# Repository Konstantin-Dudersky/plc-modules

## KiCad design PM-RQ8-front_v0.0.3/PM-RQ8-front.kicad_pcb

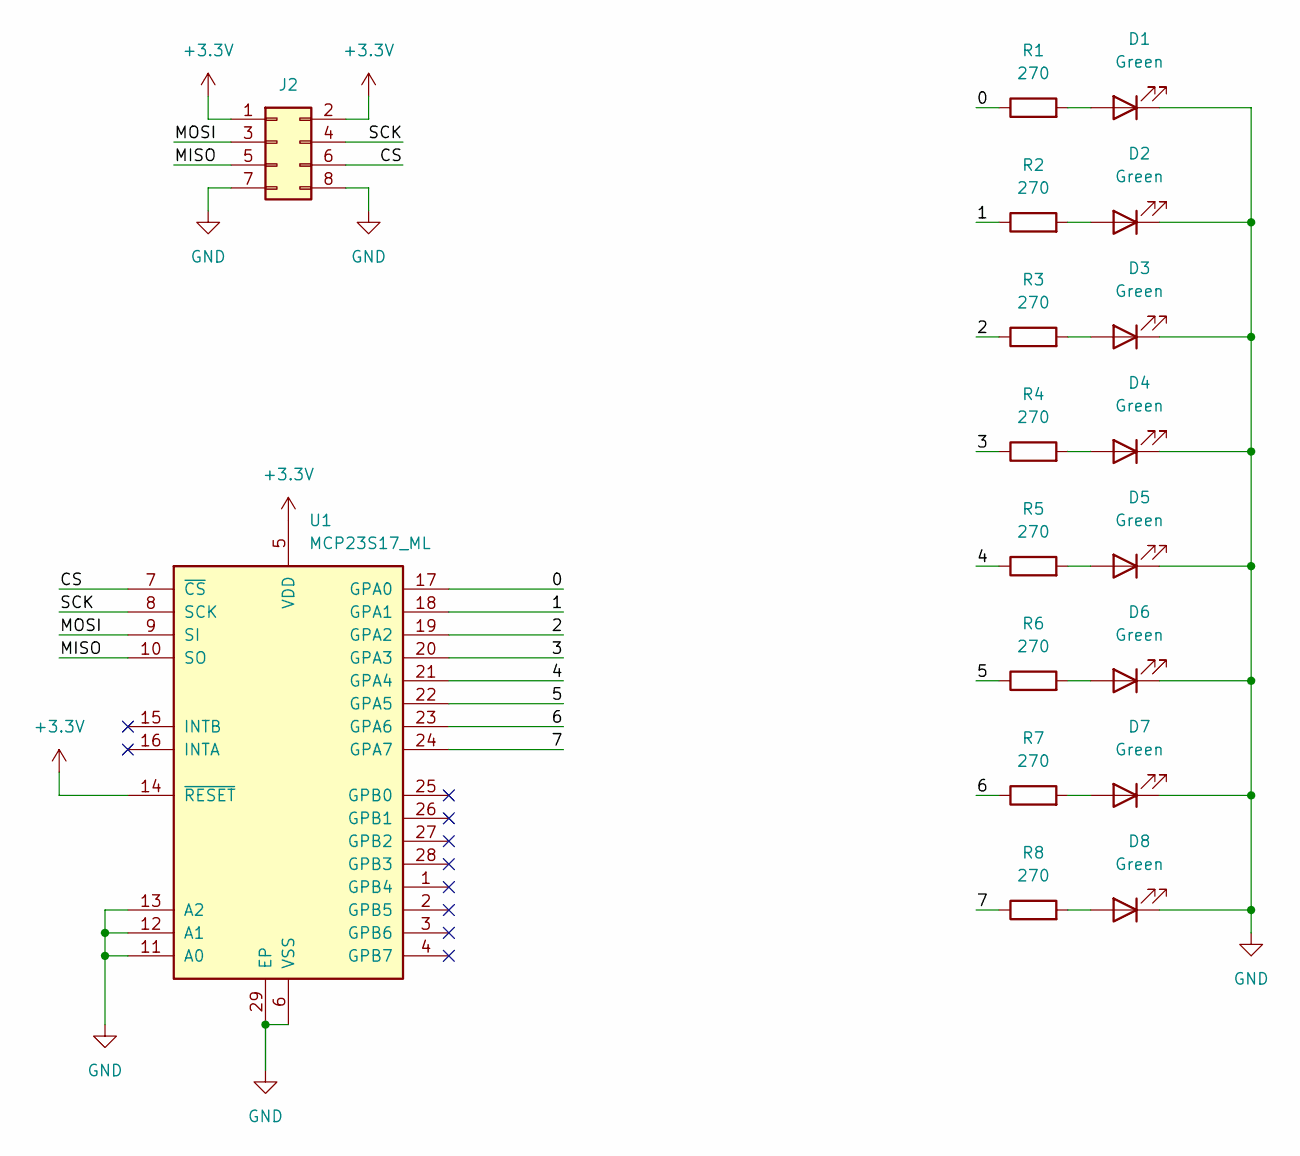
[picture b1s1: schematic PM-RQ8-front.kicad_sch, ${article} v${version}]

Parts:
D1, D2, D3, D4, D5, D6, D7, D8: Green; LED_1206_3216Metric_ReverseMount_Hole1.8x2.4mm; part_ipn LED_green_1206_reverse
J2: PinHeader_02x04_P2.54_THT_angle; PinHeader_2x04_P2.54mm_Horizontal; part_ipn PinHeader_02x04_P2.54_THT_angle
R1, R2, R3, R4, R5, R6, R7, R8: 270; R_1206_3216Metric_Pad1.30x1.75mm_HandSolder; part_ipn R_270_1206_1%
U1: MCP23S17_ML; QFN-28-1EP_6x6mm_P0.65mm_EP4.25x4.25mm; part_ipn MCP23S17-E/ML

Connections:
+3.3V: J2.1, J2.2, U1.5 (VDD), U1.14 (~RESET)
/0: R1.1, U1.17 (GPA0)
/1: R2.1, U1.18 (GPA1)
/2: R3.1, U1.19 (GPA2)
/3: R4.1, U1.20 (GPA3)
/4: R5.1, U1.21 (GPA4)
/5: R6.1, U1.22 (GPA5)
/6: R7.1, U1.23 (GPA6)
/7: R8.1, U1.24 (GPA7)
/CS: J2.6, U1.7 (~CS)
/MISO: J2.5, U1.10 (SO)
/MOSI: J2.3, U1.9 (SI)
/SCK: J2.4, U1.8 (SCK)
GND: D1.1 (K), D2.1 (K), D3.1 (K), D4.1 (K), D5.1 (K), D6.1 (K), D7.1 (K), D8.1 (K), J2.7, J2.8, U1.6 (VSS), U1.11 (A0), U1.12 (A1), U1.13 (A2), U1.29 (EP)
unnamed: D1.2 (A), R1.2
unnamed: D2.2 (A), R2.2
unnamed: D3.2 (A), R3.2
unnamed: D4.2 (A), R4.2
unnamed: D5.2 (A), R5.2
unnamed: D6.2 (A), R6.2
unnamed: D7.2 (A), R7.2
unnamed: D8.2 (A), R8.2

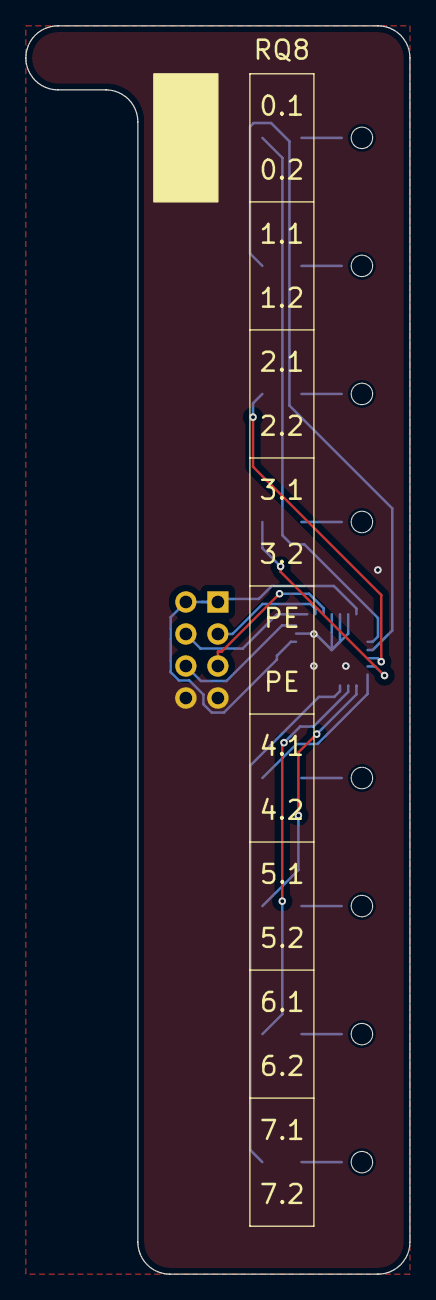
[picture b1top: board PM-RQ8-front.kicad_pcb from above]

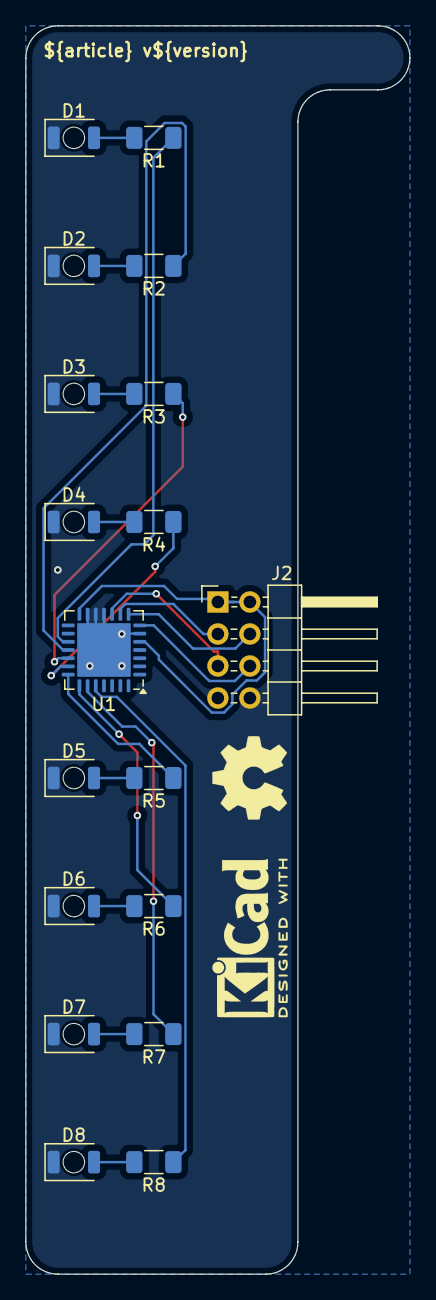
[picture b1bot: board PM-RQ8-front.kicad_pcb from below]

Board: 2 copper layers, 30.5 x 99.1 mm, 19 parts (19 on the bottom side), 22 nets.

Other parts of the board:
Logo_kicad: KiCad-Logo2_5mm_SilkScreen

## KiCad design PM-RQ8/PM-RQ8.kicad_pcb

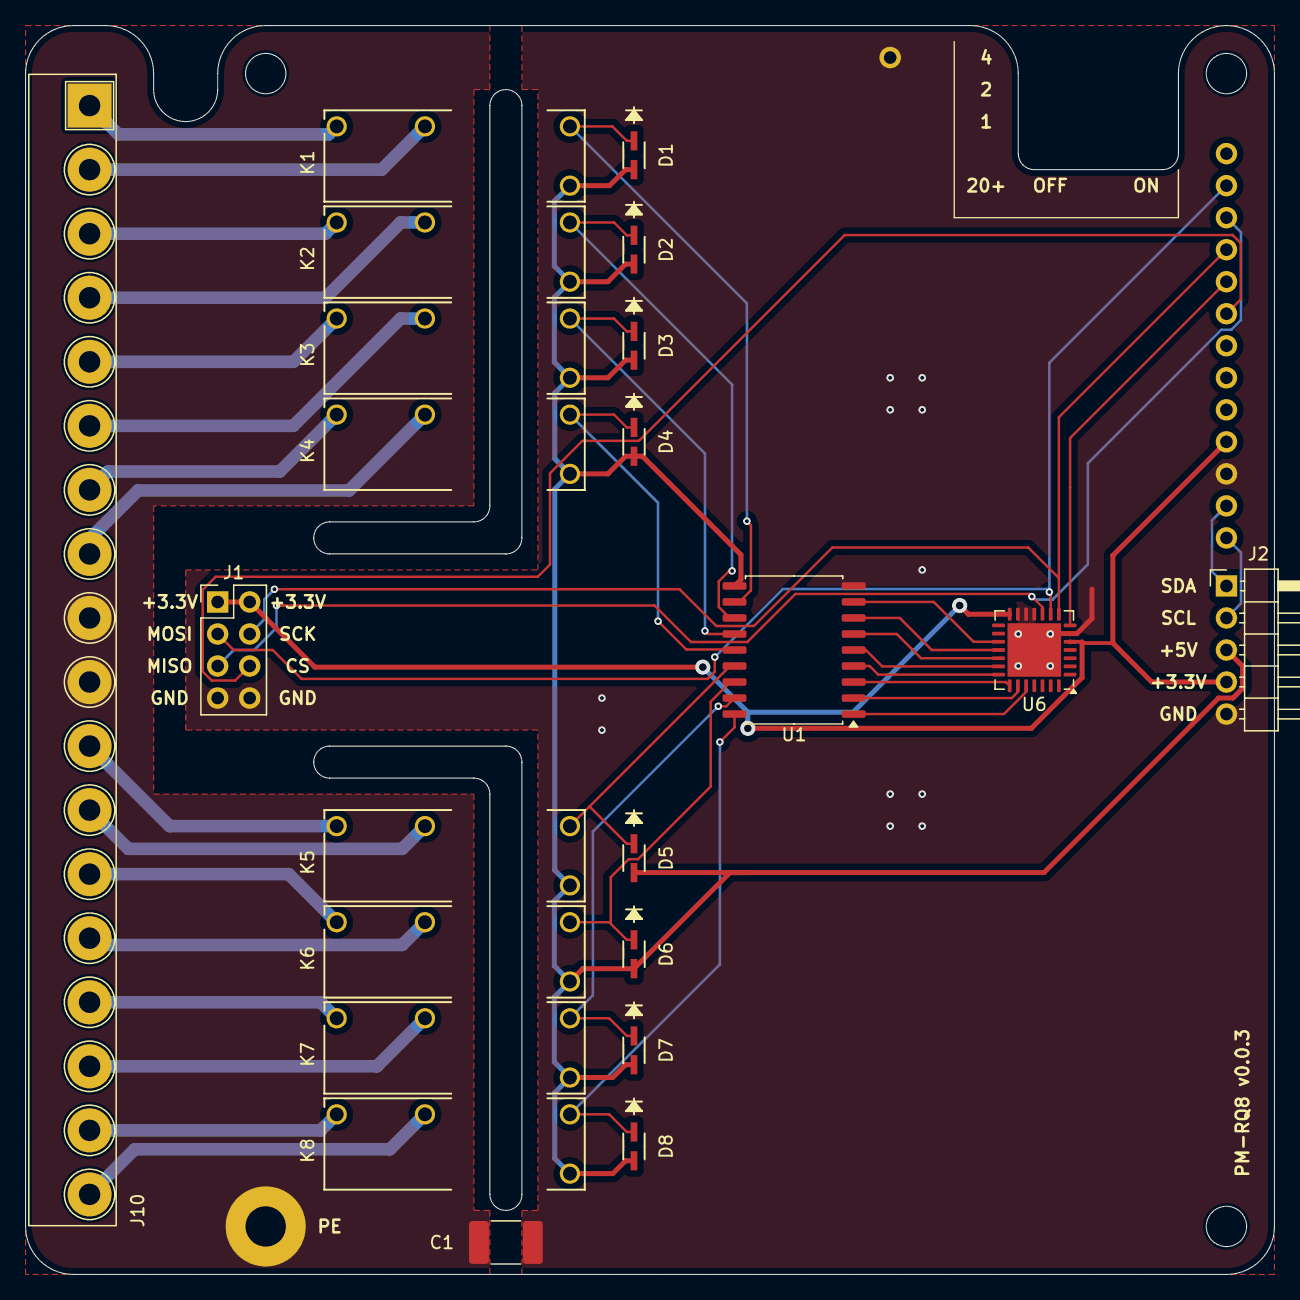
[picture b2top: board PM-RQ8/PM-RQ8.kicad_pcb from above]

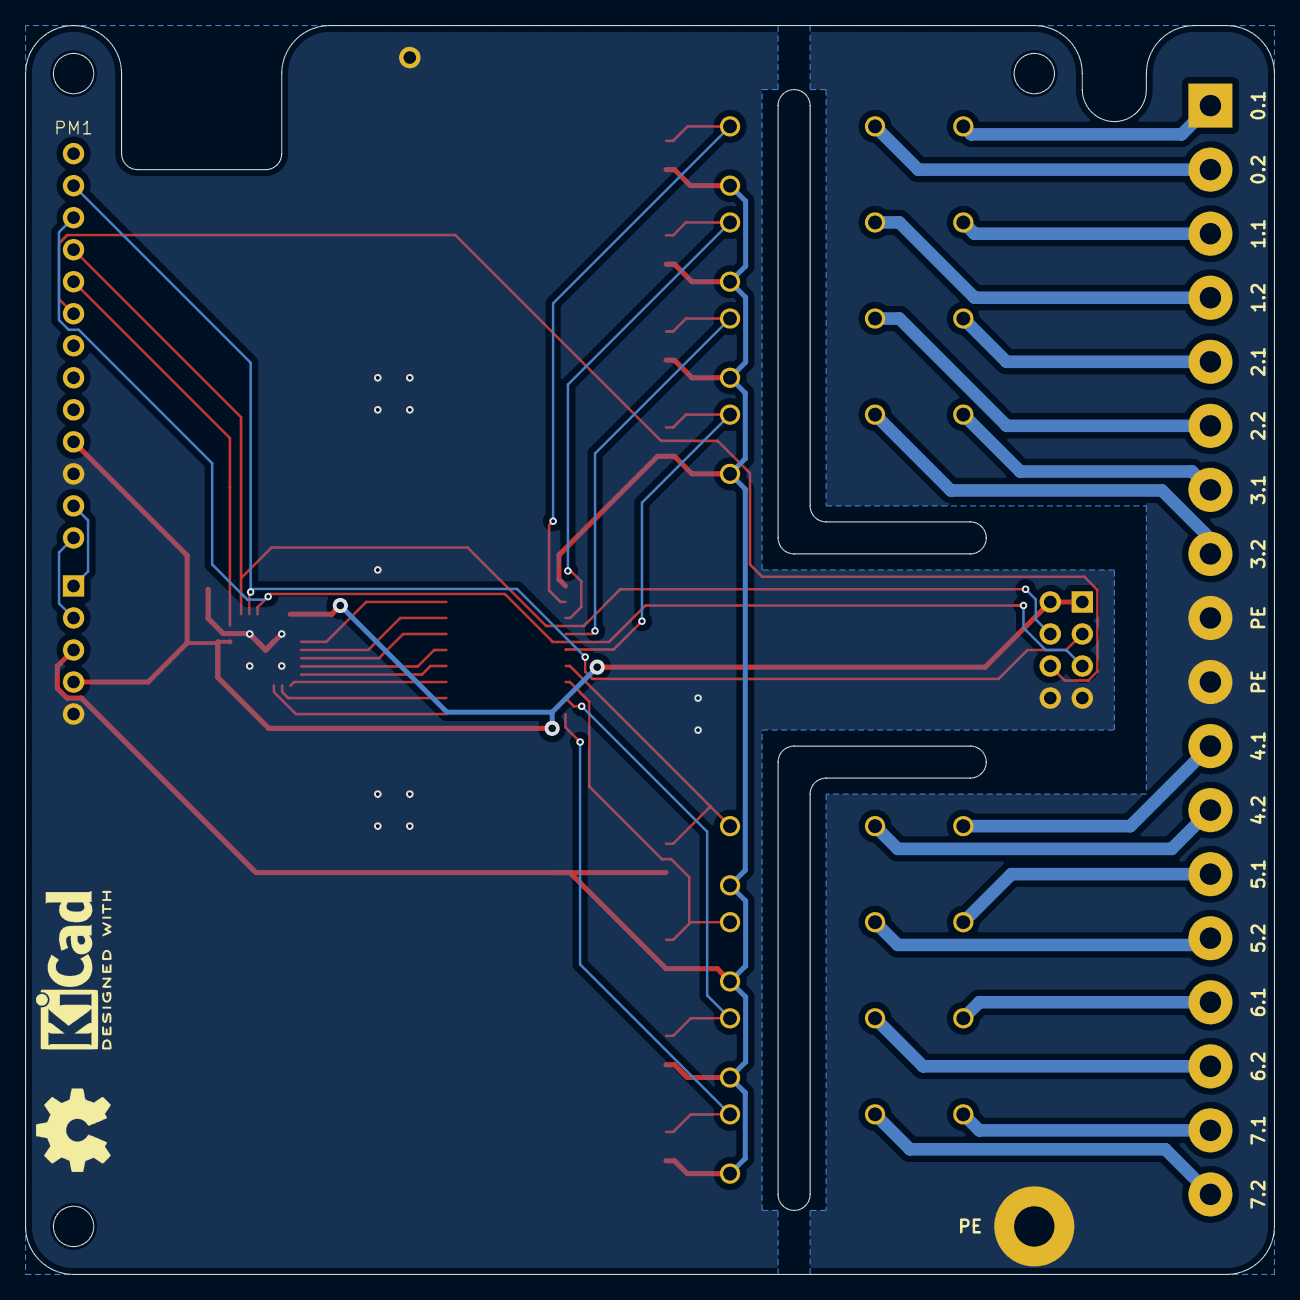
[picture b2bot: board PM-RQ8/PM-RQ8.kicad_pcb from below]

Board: 2 copper layers, 99.1 x 99.1 mm, 29 parts (3 on the bottom side), 43 nets.

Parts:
C1: 4.7nF 2kV; C_1812_4532Metric_Pad1.57x3.40mm_HandSolder
D1, D2, D3, D4, D5, D6, D7, D8: BAT20J; SOD-323_STM-M
H1, H2, H3: MountingHole; MountingHole_3.2mm_M3
J1: PM-front-02x04
J2: PinHeader_01x05_P2.54_THT_angle; PinHeader_1x05_P2.54mm_Horizontal
J10: 2EDGR-5.08-18P; Degson_2EDGR-5.08-18P
K1, K2, K3, K4, K5, K6, K7, K8: G5NB-1A-E-DC5; G5NB-1A-E_DC12_RELAY_G5NB-1A_DC5_OMR
PE1: PE
PM1: PM-ESP32C3
U1: ULN2803A
U6: MCP23S17_ML; QFN-28-1EP_6x6mm_P0.65mm_EP4.25x4.25mm
kicad_logo: KiCad-Logo2_5mm_SilkScreen
oshw_logo: OSHW-Symbol_6.7x6mm_SilkScreen

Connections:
+3.3V: J1.1, J1.2, J2.4, PM1.10 (+3.3V), U6.5 (VDD), U6.14 (~RESET)
+5V: D1.2, D2.2, D3.2, D4.2, D5.2, D6.2, D7.2, D8.2, J2.3, K1.4, K2.4, K3.4, K4.4, K5.4, K6.4, K7.4, K8.4, U1.10 (COM)
/CS1: PM1.5 (GPIO8), U6.7 (~CS)
/CS2: J1.6, PM1.6 (GPIO7)
/K1: D1.1, K1.1, U1.11 (O8)
/K1_exp: U1.8 (I8), U6.17 (GPA0)
/K2: D2.1, K2.1, U1.12 (O7)
/K2_exp: U1.7 (I7), U6.18 (GPA1)
/K3: D3.1, K3.1, U1.13 (O6)
/K3_exp: U1.6 (I6), U6.19 (GPA2)
/K4: D4.1, K4.1, U1.14 (O5)
/K4_exp: U1.5 (I5), U6.20 (GPA3)
/K5: D5.1, K5.1, U1.15 (O4)
/K5_exp: U1.4 (I4), U6.21 (GPA4)
/K6: D6.1, K6.1, U1.16 (O3)
/K6_exp: U1.3 (I3), U6.22 (GPA5)
/K7: D7.1, K7.1, U1.17 (O2)
/K7_exp: U1.2 (I2), U6.23 (GPA6)
/K8: D8.1, K8.1, U1.18 (O1)
/K8_exp: U1.1 (I1), U6.24 (GPA7)
/MISO: J1.5, PM1.3 (GPIO3), U6.10 (SO)
/MOSI: J1.3, PM1.2 (GPIO2), U6.9 (SI)
/SCK: J1.4, PM1.4 (GPIO9), U6.8 (SCK)
/SCL: J2.2, PM1.13 (SCL)
/SDA: J2.1, PM1.12 (SDA)
GND: C1.2, J1.7, J1.8, J2.5, PM1.11 (GND), PM1.14 (GND), U1.9 (GND), U6.6 (VSS), U6.11 (A0), U6.12 (A1), U6.13 (A2), U6.29 (EP)
unnamed: J10.1, K1.3
unnamed: J10.2, K1.2
unnamed: J10.3, K2.3
unnamed: J10.4, K2.2
unnamed: J10.5, K3.3
unnamed: J10.6, K3.2
unnamed: J10.7, K4.3
unnamed: J10.8, K4.2
unnamed: J10.11, K5.3
unnamed: J10.12, K5.2
unnamed: J10.13, K6.3
unnamed: J10.14, K6.2
unnamed: J10.15, K7.3
unnamed: J10.16, K7.2
unnamed: J10.17, K8.3
unnamed: J10.18, K8.2
PE: C1.1, J10.9, J10.10, PE1.1

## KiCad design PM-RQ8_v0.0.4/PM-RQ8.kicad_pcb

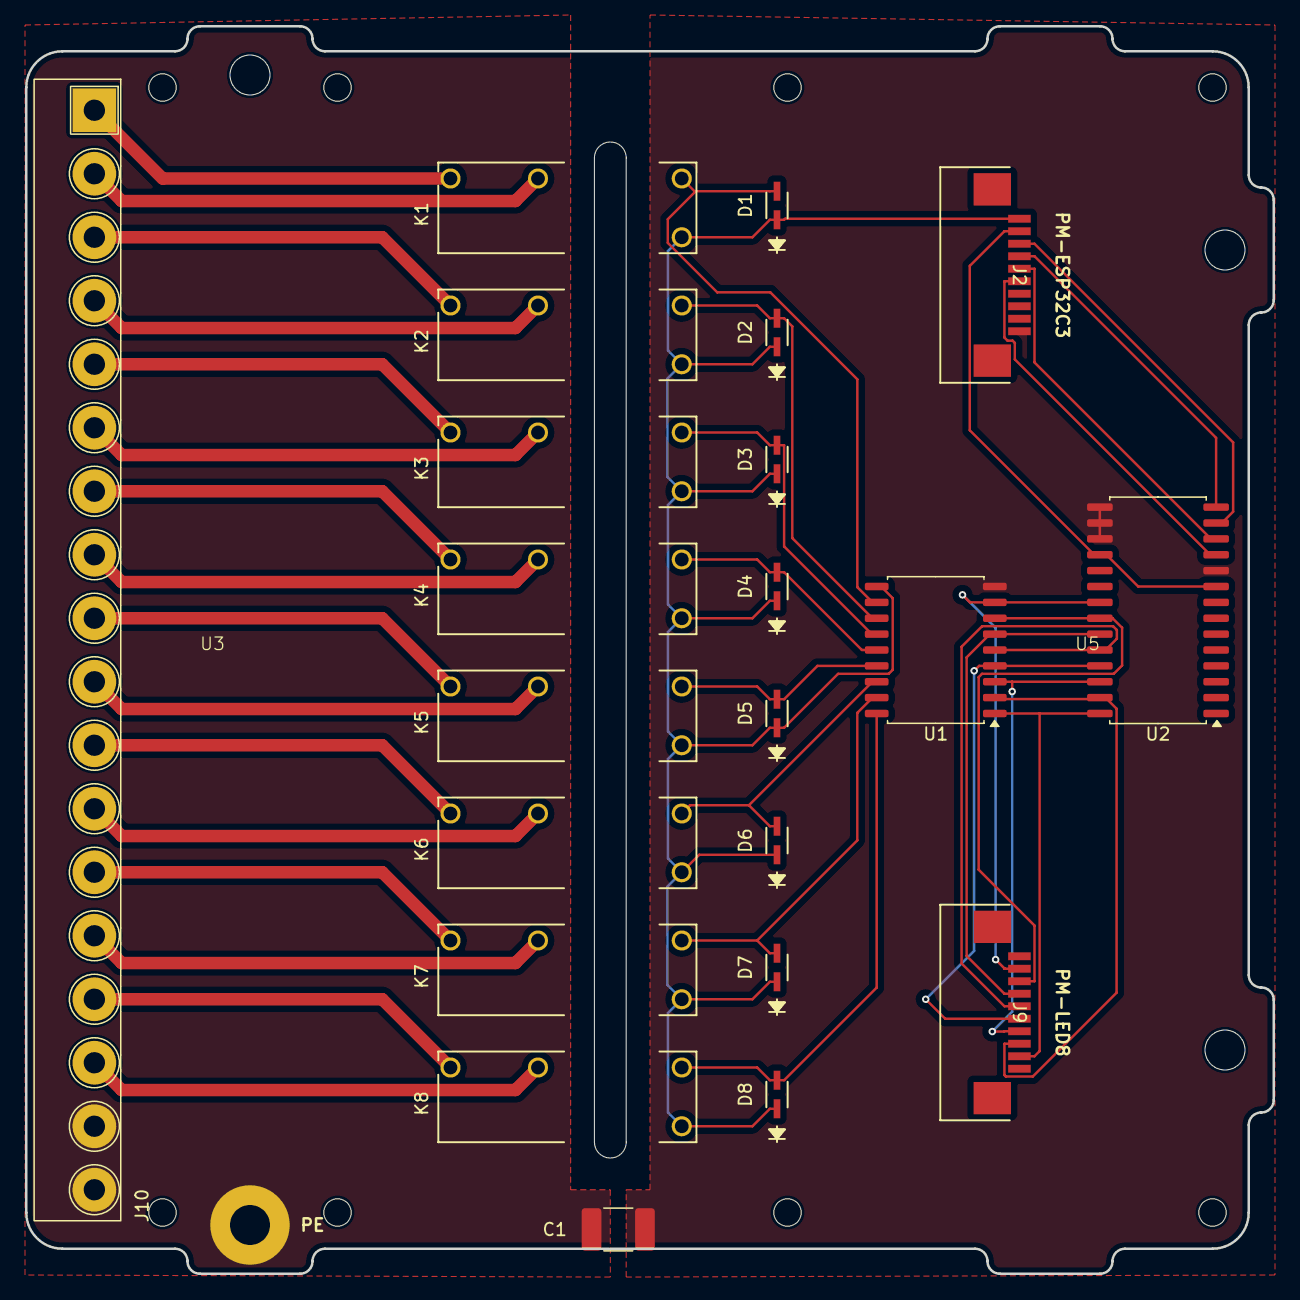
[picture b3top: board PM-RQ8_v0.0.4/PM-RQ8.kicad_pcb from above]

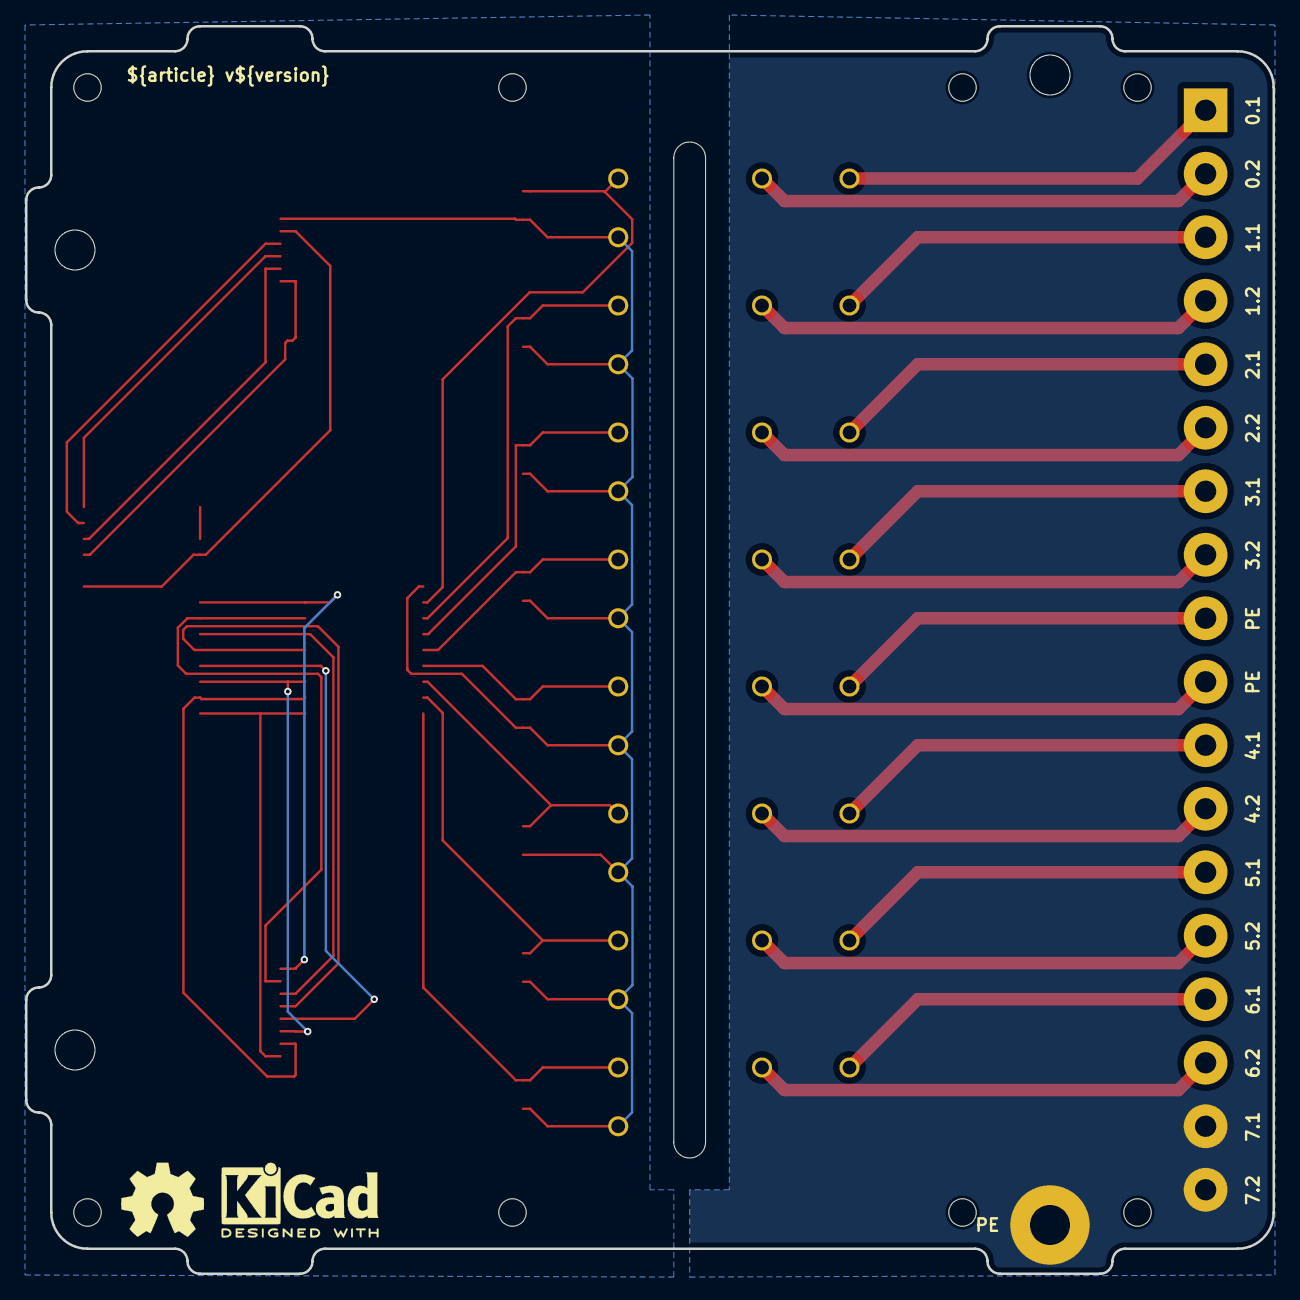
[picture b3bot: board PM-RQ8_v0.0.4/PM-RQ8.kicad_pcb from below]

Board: 2 copper layers, 99.8 x 99.8 mm, 30 parts (2 on the bottom side), 40 nets.

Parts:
C1: 4.7nF 2kV; C_1812_4532Metric_Pad1.57x3.40mm_HandSolder
D1, D2, D3, D4, D5, D6, D7, D8: BAT20J; SOD-323_STM-M
H1, H2, H3: MountingHole; MountingHole_3.2mm_M3
J2, J9: AFA07-S10FCC-00; CONN10_AFA07-S10_JUS
J10: 2EDGR-5.08-18P; Degson_2EDGR-5.08-18P
K1, K2, K3, K4, K5, K6, K7, K8: G5NB-1A-E-DC5; G5NB-1A-E_DC12_RELAY_G5NB-1A_DC5_OMR
PE1: PE
U1: ULN2803A
U2: MCP23S17_SO; SOIC-28W_7.5x17.9mm_P1.27mm
U3: PM-LED8_v0.0.1; PM-LED_v0.0.1
U5: PM-ESP32C3_v0.0.2
kicad_logo: KiCad-Logo2_5mm_SilkScreen
oshw_logo: OSHW-Symbol_6.7x6mm_SilkScreen

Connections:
+3.3V: J2.2, U2.9 (VDD), U2.18 (~RESET)
+5V: D1.1, D2.1, D3.1, D4.1, D5.1, D6.1, D7.1, D8.1, J2.1, K1.4, K2.4, K3.4, K4.4, K5.4, K6.4, K7.4, K8.4, U1.10 (COM)
/CS: J2.6, U2.11 (~CS)
/K1: D1.2, K1.1, U1.11 (O8)
/K1_exp: J9.2, U1.8 (I8), U2.21 (GPA0)
/K2: D2.2, K2.1, U1.12 (O7)
/K2_exp: J9.3, U1.7 (I7), U2.22 (GPA1)
/K3: D3.2, K3.1, U1.13 (O6)
/K3_exp: J9.4, U1.6 (I6), U2.23 (GPA2)
/K4: D4.2, K4.1, U1.14 (O5)
/K4_exp: J9.5, U1.5 (I5), U2.24 (GPA3)
/K5: D5.2, K5.1, U1.15 (O4)
/K5_exp: J9.6, U1.4 (I4), U2.25 (GPA4)
/K6: D6.2, K6.1, U1.16 (O3)
/K6_exp: J9.7, U1.3 (I3), U2.26 (GPA5)
/K7: D7.2, K7.1, U1.17 (O2)
/K7_exp: J9.8, U1.2 (I2), U2.27 (GPA6)
/K8: D8.2, K8.1, U1.18 (O1)
/K8_exp: J9.9, U1.1 (I1), U2.28 (GPA7)
/MISO: J2.4, U2.14 (SO)
/MOSI: J2.3, U2.13 (SI)
/SCK: J2.5, U2.12 (SCK)
GND: C1.2, J2.10, J9.10, U1.9 (GND), U2.10 (VSS), U2.15 (A0), U2.16 (A1), U2.17 (A2)
unnamed: J10.1, K1.3
unnamed: J10.2, K1.2
unnamed: J10.3, K2.3
unnamed: J10.4, K2.2
unnamed: J10.5, K3.3
unnamed: J10.6, K3.2
unnamed: J10.7, K4.3
unnamed: J10.8, K4.2
unnamed: J10.9, K5.3
unnamed: J10.10, K5.2
unnamed: J10.11, K6.3
unnamed: J10.12, K6.2
unnamed: J10.13, K7.3
unnamed: J10.14, K7.2
unnamed: J10.15, K8.3
unnamed: J10.16, K8.2
PE: C1.1, J10.17, J10.18, PE1.1

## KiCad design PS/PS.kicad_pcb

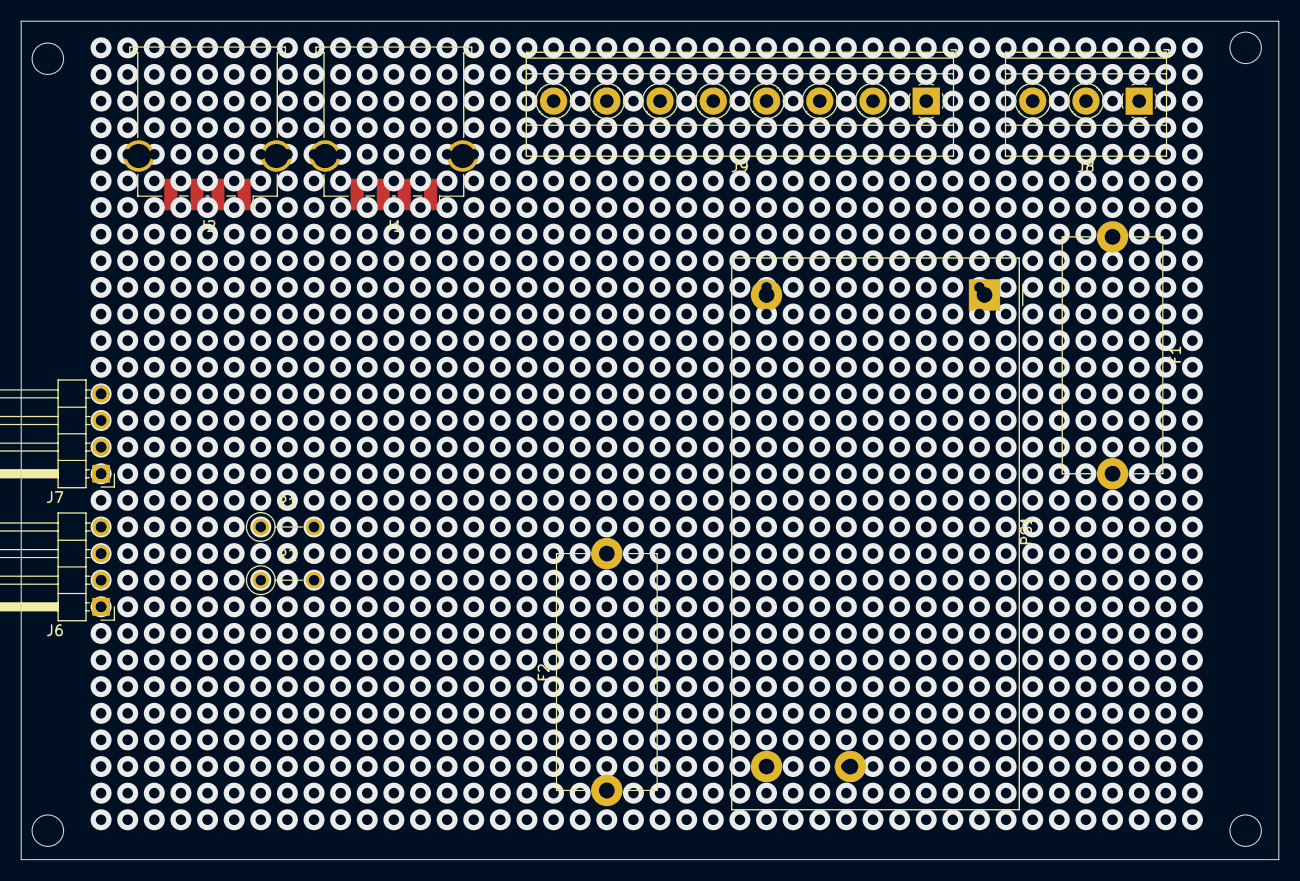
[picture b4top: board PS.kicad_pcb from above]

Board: 2 copper layers, 120.0 x 80.0 mm, 11 parts (0 on the bottom side), 9 nets, no tracks yet.

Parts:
F1, F2: Fuse; Fuseholder_Cylinder-5x20mm_Stelvio-Kontek_PTF78_Horizontal_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
J1, J2: USB_A; USB_A_TE_292303-7_Horizontal
J6, J7: PinHeader_01x04_angle; PinHeader_1x04_P2.54mm_Horizontal
J8: Conn_01x03_Socket; TerminalBlock_Phoenix_MKDS-1,5-3-5.08_1x03_P5.08mm_Horizont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
J9: Terminal_01x08_Socket; TerminalBlock_Phoenix_MKDS-1,5-8-5.08_1x08_P5.08mm_Horizont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
PS1: IRM-20-5; Converter_ACDC_MeanWell_IRM-20-xx_THT
R1, R2: 3.3к; R_Axial_DIN0207_L6.3mm_D2.5mm_P5.08mm_Vertical

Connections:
/3.3V: J7.2, R1.2, R2.2
/5V: F2.2, J1.1 (VBUS), J2.1 (VBUS), J6.2, J9.1, J9.3
/GND: J1.4 (GND), J2.4 (GND), J6.3, J9.2, J9.4, PS1.3 (-Vo)
/SCL: J6.1, J7.1, R2.1
/SDA: J6.4, J7.3, R1.1
unnamed: F1.1, J8.1
unnamed: J8.2, PS1.2 (AC/N)
unnamed: F2.1, PS1.4 (+Vo)
unnamed: F1.2, PS1.1 (AC/L)

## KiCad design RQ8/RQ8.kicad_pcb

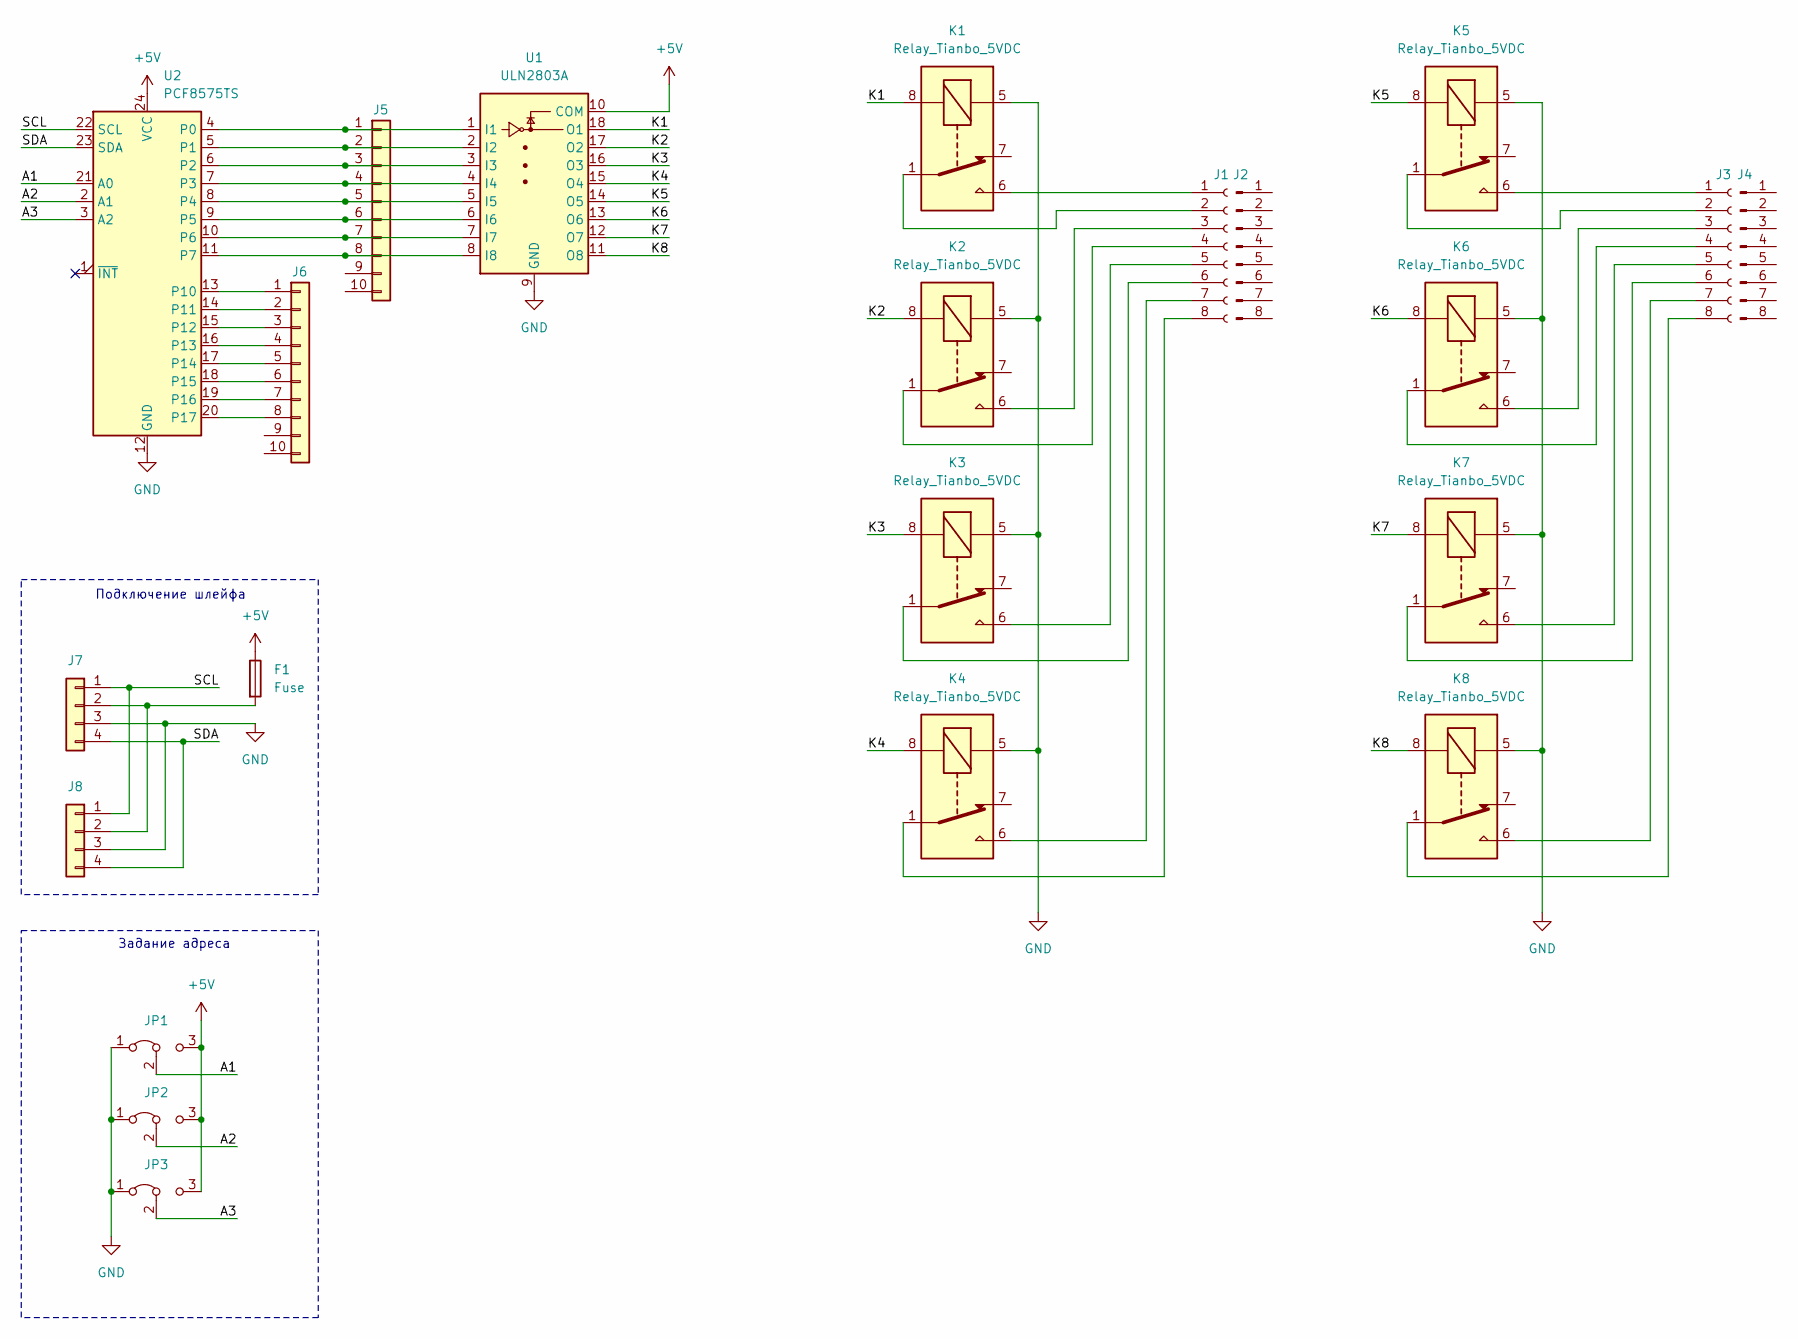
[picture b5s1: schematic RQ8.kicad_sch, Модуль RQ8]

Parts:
F1: Fuse; Fuseholder_Cylinder-5x20mm_Stelvio-Kontek_PTF78_Horizontal_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
J1, J3: Terminal_01x08_Socket; TerminalBlock_Phoenix_MKDS-1,5-8-5.08_1x08_P5.08mm_Horizont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
J2, J4: Conn_01x08_Pin
J5, J6: Conn_01x10; PinHeader_1x10_P2.54mm_Vertical
J7, J8: PinHeader_01x04_angle; PinHeader_1x04_P2.54mm_Horizontal
JP1, JP2, JP3: Jumper_3_Bridged12; PinHeader_1x03_P2.54mm_Vertical
K1, K2, K3, K4, K5, K6, K7, K8: Relay_Tianbo_5VDC; Relay_SPDT_HJR-4102
U1: ULN2803A; DIP-18_W7.62mm
U2: PCF8575TS; SSOP-24_5.3x8.2mm_P0.65mm

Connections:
+5V: F1.1, JP1.3 (B), JP2.3 (B), JP3.3 (B), U1.10 (COM), U2.24 (VCC)
/A1: JP1.2 (C), U2.21 (A0)
/A2: JP2.2 (C), U2.2 (A1)
/A3: JP3.2 (C), U2.3 (A2)
/K1: K1.8, U1.18 (O1)
/K2: K2.8, U1.17 (O2)
/K3: K3.8, U1.16 (O3)
/K4: K4.8, U1.15 (O4)
/K5: K5.8, U1.14 (O5)
/K6: K6.8, U1.13 (O6)
/K7: K7.8, U1.12 (O7)
/K8: K8.8, U1.11 (O8)
/SCL: J7.1, J8.1, U2.22 (SCL)
/SDA: J7.4, J8.4, U2.23 (SDA)
GND: J7.3, J8.3, JP1.1 (A), JP2.1 (A), JP3.1 (A), K1.5, K2.5, K3.5, K4.5, K5.5, K6.5, K7.5, K8.5, U1.9 (GND), U2.12 (GND)
unnamed: J1.1, K1.6
unnamed: J1.2, K1.1
unnamed: J1.3, K2.6
unnamed: J1.4, K2.1
unnamed: J1.5, K3.6
unnamed: J1.6, K3.1
unnamed: J1.7, K4.6
unnamed: J1.8, K4.1
unnamed: J3.1, K5.6
unnamed: J3.2, K5.1
unnamed: J3.3, K6.6
unnamed: J3.4, K6.1
unnamed: J3.5, K7.6
unnamed: J3.6, K7.1
unnamed: J3.7, K8.6
unnamed: J3.8, K8.1
unnamed: J5.1, U1.1 (I1), U2.4 (P0)
unnamed: J5.2, U1.2 (I2), U2.5 (P1)
unnamed: J5.3, U1.3 (I3), U2.6 (P2)
unnamed: J5.4, U1.4 (I4), U2.7 (P3)
unnamed: J5.5, U1.5 (I5), U2.8 (P4)
unnamed: J5.6, U1.6 (I6), U2.9 (P5)
unnamed: J5.7, U1.7 (I7), U2.10 (P6)
unnamed: J5.8, U1.8 (I8), U2.11 (P7)
unnamed: J6.1, U2.13 (P10)
unnamed: J6.2, U2.14 (P11)
unnamed: J6.3, U2.15 (P12)
unnamed: J6.4, U2.16 (P13)
unnamed: J6.5, U2.17 (P14)
unnamed: J6.6, U2.18 (P15)
unnamed: J6.7, U2.19 (P16)
unnamed: J6.8, U2.20 (P17)
unnamed: F1.2, J7.2, J8.2

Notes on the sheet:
Задание адреса
Подключение шлейфа

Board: 2 copper layers, 20 parts (0 on the bottom side), 48 nets, no tracks yet.

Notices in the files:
parts and their libraries:
COPYRIGHT: Copyright (C) 2023 Ultra Librarian. All rights reserved.
